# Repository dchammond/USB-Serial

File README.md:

# USB-Serial
KiCad USB-Serial Project

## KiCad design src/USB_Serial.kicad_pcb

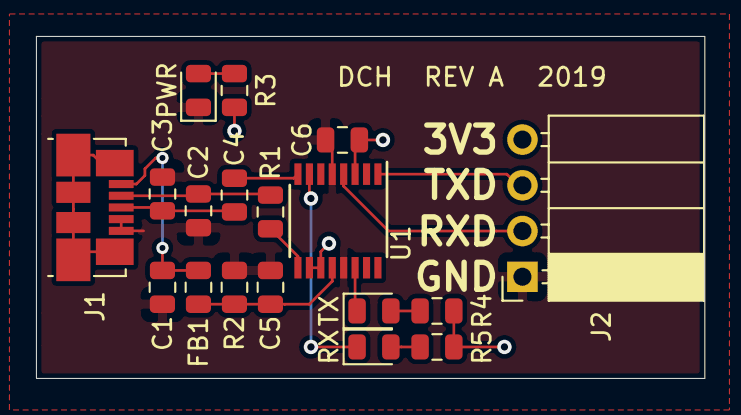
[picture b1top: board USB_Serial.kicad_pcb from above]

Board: 2 copper layers, 37.1 x 19.0 mm, 18 parts (0 on the bottom side), 15 nets.

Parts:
C1: 10nF; C_0805_2012Metric
C2, C3: 47pF; C_0805_2012Metric
C4, C6: 100nF; C_0805_2012Metric
C5: 4.7uF; C_0805_2012Metric
FB1: FB; L_0805_2012Metric
J1: USB_B_Micro; USB_Micro-B_Molex_47346-0001
J2: UART; PinSocket_1x04_P2.54mm_Horizontal
PWR: LED; LED_0805_2012Metric
R1, R2: 27R; R_0805_2012Metric
R3, R4, R5: 1K; R_0805_2012Metric
RX: LED; LED_0805_2012Metric
TX: LED; LED_0805_2012Metric
U1: FT230XS; SSOP-16_3.9x4.9mm_P0.635mm

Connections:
+3V3: C6.2, J2.4, R3.1, R4.2, R5.2, U1.3, U1.10, U1.11
+5V: C4.2, C5.2, FB1.2, U1.12
/D+: C3.2, J1.3, R2.1
/D-: C2.2, J1.2, R1.1
/RXLED: RX.1, U1.7
/TXLED: TX.1, U1.14
/USBD+: R2.2, U1.8
/USBD-: R1.2, U1.9
/VBUS: C1.2, FB1.1, J1.1
GND: C1.1, C2.1, C3.1, C4.1, C5.1, C6.1, J1.4, J1.5, J2.1, PWR.1, U1.5, U1.13
unnamed: R4.1, TX.2
unnamed: R5.1, RX.2
unnamed: PWR.2, R3.2
unnamed: J2.2, U1.4
unnamed: J2.3, U1.1

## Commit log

2019-11-14 Rev A
2019-11-14 proeprly saved file
